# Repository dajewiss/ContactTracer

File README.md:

# ContactTracer
Trace contacts using a Bluetooth device to log when people pass

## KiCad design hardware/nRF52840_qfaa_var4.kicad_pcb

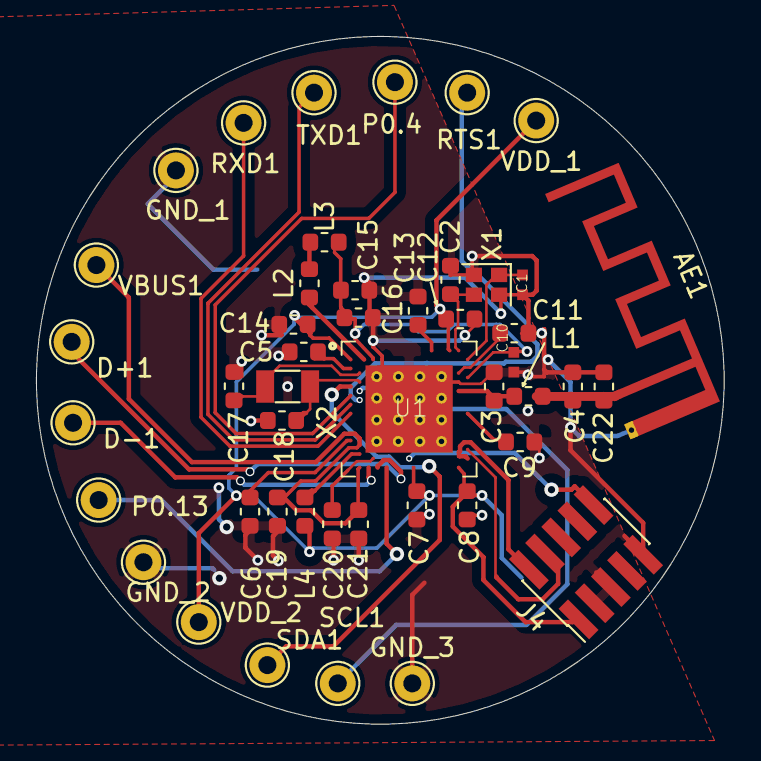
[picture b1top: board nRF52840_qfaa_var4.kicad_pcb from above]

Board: 2 copper layers, 38.2 x 38.2 mm, 47 parts (0 on the bottom side), 30 nets.

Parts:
AE1: Antenna_Shield; Texas_SWRA117D_2.4GHz_Left
BT1: Battery_Cell; BatteryHolder_Keystone_1058_1x2032
C1: 12pF; RESC0402_N
C2, C17: 12pF; C_0603_1608Metric
C3, C4: 1pF; C_0603_1608Metric
C5, C7, C8, C12: 100nF; C_0603_1608Metric
C6, C14, C19, C20, C21: 4.7µF; C_0603_1608Metric
C9: 820pF; C_0603_1608Metric
C10: N.C.; RESC0402_N
C11: 100pF; C_0603_1608Metric
C13, C22: N.C.; C_0603_1608Metric
C15: 1.0µF; C_0603_1608Metric
C16: 47nF; C_0603_1608Metric
C18: 12pF; R_0603_1608Metric
D+1: TestPoint; TestPoint_THTPad_D2.0mm_Drill1.0mm
D-1: TestPoint; TestPoint_THTPad_D2.0mm_Drill1.0mm
GND_1, GND_2, GND_3: TestPoint; TestPoint_THTPad_D2.0mm_Drill1.0mm
J4: Conn_02x05_Odd_Even; PinHeader_2x05_P1.27mm_Vertical_SMD
L1: 3.9nH; L_0603_1608Metric
L2: 10µH; L_0603_1608Metric
L3: 15nH; L_0603_1608Metric
L4: 10µH; C_0603_1608Metric
P0.4, P0.13: TestPoint; TestPoint_THTPad_D2.0mm_Drill1.0mm
RTS1: TestPoint; TestPoint_THTPad_D2.0mm_Drill1.0mm
RXD1: TestPoint; TestPoint_THTPad_D2.0mm_Drill1.0mm
SCL1: TestPoint; TestPoint_THTPad_D2.0mm_Drill1.0mm
SDA1: TestPoint; TestPoint_THTPad_D2.0mm_Drill1.0mm
TXD1: TestPoint; TestPoint_THTPad_D2.0mm_Drill1.0mm
U1: NRF52840_QF; AQFN50P700X700X85_HS-74N
VBUS1: TestPoint; TestPoint_THTPad_D2.0mm_Drill1.0mm
VDD_1, VDD_2: TestPoint; TestPoint_THTPad_D2.0mm_Drill1.0mm
X1: 32MHz; Crystal_SMD_2016-4Pin_2.0x1.6mm
X2: 32.768kHz; Crystal_SMD_3215-2Pin_3.2x1.5mm

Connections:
/D+: D+1.1, U1.P$AD6
/D-: D-1.1, U1.P$AD4
/DEC1: C5.1, U1.P$C1
/DEC3: C11.1, U1.P$D23
/DEC4_6: C10.1, C15.1, C16.1, L3.2, U1.P$B5, U1.P$E24
/P0.00/XL1: C17.2, U1.P$D2, X2.1
/P0.01/XL2: C18.2, U1.P$F2, X2.2
/P0.04: P0.4.1, U1.P$J1
/P0.13: P0.13.1, U1.P$AD8
/P0.18_RESET: J4.10, U1.P$AC13
/RF: AE1.1, C4.1, C22.1, L1.2
/RTS: RTS1.1, U1.P$K2
/RXD: RXD1.1, U1.P$N1
/SCL: SCL1.1, U1.P$H2
/SDA: SDA1.1, U1.P$G1
/SWDCLK: J4.4, U1.P$AA24
/SWDIO: J4.2, U1.P$AC24
/TXD: TXD1.1, U1.P$L1
GND: AE1.2, BT1.2, C1.2, C2.2, C3.2, C4.2, C5.2, C6.2, C7.2, C8.2, C9.2, C10.2, C11.2, C12.2, C13.2, C14.2, C15.2, C16.2, C17.1, C18.1, C19.2, C20.2, C21.2, C22.2, GND_1.1, GND_2.1, GND_3.1, J4.3, J4.5, J4.9, U1.P$74, U1.P$75, U1.P$76, U1.P$77, U1.P$78, U1.P$79, U1.P$80, U1.P$81, U1.P$82, U1.P$83, U1.P$84, U1.P$85, U1.P$86, U1.P$87, U1.P$88, U1.P$89, U1.P$90, U1.P$B7, U1.P$F23, X1.2, X1.4
unnamed: C1.1, U1.P$B24, X1.1
unnamed: C2.1, U1.P$A23, X1.3
unnamed: C3.1, L1.1, U1.P$H23
unnamed: C9.1, U1.P$N24
unnamed: C13.1, U1.P$A18
unnamed: C20.1, U1.P$AC5
unnamed: L2.1, U1.P$B3
unnamed: L2.2, L3.1
unnamed: L4.2, U1.P$AB2
VCC: BT1.1, C6.1, C7.1, C8.1, C12.1, C14.1, J4.1, L4.1, U1.P$A22, U1.P$AD14, U1.P$AD23, U1.P$B1, U1.P$W1, VDD_1.1, VDD_2.1
VEE: C19.1, C21.1, U1.P$AD2, U1.P$Y2, VBUS1.1

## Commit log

2020-07-08 set up driectories for repo
